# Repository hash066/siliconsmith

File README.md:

<div align="center">

# Hardwright

**Agents that design hardware, and prove it.**

<sub>Click the animation to watch the full demo video on YouTube.</sub>

[**Try it, no sign-up**](https://siliconsmith.vercel.app) · [**Watch the demo**](https://youtu.be/6LJNFYmQQWk) · [**Use it from your agent**](https://siliconsmith.vercel.app/connect) · [Feedback on Nebius](docs/feedback.md) · [Model comparison](docs/MODEL_COMPARISON.md)

</div>

Hardwright is a workstation for people who make hardware: describe a heat sink, a sensor board or a slow loop in plain words, and a
Nemotron agent builds it. Every claim it makes has to pass a checker it cannot argue with, so you get a part, a board or an instruction
you can open in a real tool, plus the evidence for it. It also ships as an **open-source Python package, command-line tool and MCP server**
so any coding agent can use the same checkers.

> Built for the Nebius x NVIDIA Global AI Hackathon (Coding and Agentic Engineering) · Apache-2.0

```bash
pip install "hardwright[matter] @ git+https://github.com/hash066/siliconsmith#subdirectory=engine"
claude mcp add hardwright -- hardwright mcp        # or: codex mcp add ... / Cursor / VS Code (see /connect)
hardwright board check --template fault_gpio12_vs_gpio14     # exit 1: the firmware uses a boot-strapping pin
```

---

## Three workbenches, one idea

The idea: **an AI may say what it likes, but it may only claim what a deterministic verifier returned.** Each workbench ends in something
you can open in a real tool, and each result carries the tool, the version and the verdict behind it.

| Workbench | You say | You get | Verified by |
|---|---|---|---|
| **Board** | "A battery ESP32 sensor board with a BME280 and USB-C charging; check it against its firmware." | A **routed 2-layer KiCad board** you can zoom, a schematic, a report card, Gerbers, KiCad file, BOM, pick-and-place. The wrong pin is marked on the pad. | Five netlist checks (B1 to B5: well formed, electrical rules, bus rules, firmware pins vs netlist and boot-strapping hazards, battery estimate), KiCad 7 design-rule check, the autorouter's completion |
| **Matter** | "A heat sink for a 5 W chip, 40 mm square, under 70 C." | A 3D part coloured by temperature, a printable **STL**, and a side-by-side with plain fins that use the same material | A finite-volume solver validated on analytic cases, an independent finite-element solver, printability rules, equal-material baselines (M1 to M5) |
| **Silicon** | "Make this loop faster with a custom RISC-V instruction." | A new instruction written **live**: Verilog, C intrinsic, rewritten kernel, a circuit view of the hardware, a waveform on real operand pairs, a before/after loop | Verilator lint, 1,000,000 test vectors, a **Yosys SAT proof for every possible input**, whole-program output check, cycle count and area |

Around them: a **chat agent** (Nemotron 3 Ultra, Super and Nano on Nebius Token Factory, with native tool calling) that performs actions in the app
and reports what it spent; **projects** (each workbench is a folder of projects with its own chat and settings); a **Workflow** tab that shows every
project as connected steps with their real status; a **Verified-by ledger** on every Proof tab; **one-click zip** of a project; and $0.50 of demo
credit per visitor from a $25 pool.

### See it

| Matter | Board |
|---|---|
|  |  |
| **Board, catching a mistake** | **Silicon** |
|  |  |

## What is real

Everything below ran for real and is reproducible; numbers are from the run logs and the test suites.

* **Board.** The three example boards (clean, wiring fault, strapping-pin fault) route fully with **0 KiCad errors** (15 silkscreen warnings), 48 × 36 mm.
  Boards for **any** design are made on request in a **Token Factory Sandbox** that has KiCad, Java and Freerouting: a custom design routed in **107 s**
  with 0 errors, measured on the public site. Placement is deterministic code (not a model), so a board is reproducible. Pin tables are cross-checked
  against KiCad's own symbol library. The checker is tested against a catalogue of 8 injected wiring faults.
* **Silicon, live.** A real run on the public site: Nemotron Ultra proposes, Super implements, a Sandbox proves it. TinyMaix int8 dot product:
  **3.32× fewer cycles for +4.8% area** (another run 2.69×), about 2 minutes and $0.04 of model tokens; ChaCha20: 1.14×. The recorded 20-minute full searches
  (with clock-speed estimates) reached **4.04× cycles / 3.76× wall-clock** on TinyMaix ([pull request](https://github.com/hash066/TinyMaix/pull/1)).
* **Matter.** Gains over an equal-material plain-fin plate are small and we say so: +0.1 to +0.5 K in the recorded evaluations, and the app will show a loss
  ("1.3 K hotter than plain fins") rather than hide it.
* **Tests.** Engine 640 passed (14 skipped), web 339 passed, axe accessibility 0 violations, layout shift 0.03, strict first-time-user pass in
  `docs/EVALUATION.md`.

## Honest limits

* The board check is **netlist level**. It does not prove a board works; the routed board is **not fabricated or tested electrically**. Part facts are
  author-curated, each with a `citation_checked` flag. 2 layers, 0.2 mm tracks, 0.15 mm clearance.
* Matter is **2D steady state** with stated constants: not CFD, not a measurement. "Validated" means agreement with analytic cases, nothing more.
* A live Silicon run skips clock-speed (place and route) so it reports **cycles and area, not wall-clock**; the recorded searches do include it.
  The FPGA rung (L6) was not run on a board. Software calls the instruction through inline assembly, not a compiler backend.
* The agent can be wrong: its answers are checked against the verifiers and say so when a check fails. Rate limits and the shared credit pool are per server instance.
* Run-to-run variance is real and published: TinyMaix wall-clock across our runs ranged 3.17× to 3.86×.

## Use it from your coding agent

The `hardwright` package (in `engine/`, Apache-2.0) is offline and free: no model, no network, no API key. Every check answers `pass`, `fail` or `unknown`;
only `pass` is a claim.

```python
import hardwright as hw
hw.board_check(template="fault_gpio12_vs_gpio14")["passed"]                       # False (B4)
hw.board_fix_pin(template="fault_gpio12_vs_gpio14", function="wake_btn", pin="GPIO14")["passed"]   # True
hw.matter_simulate(power_w=5, stl_path="heat-sink.stl")["peak_c"]
```

MCP tools: `board_templates`, `board_get_template`, `board_check`, `board_fix_pin`, `board_parts`, `matter_simulate`. Verified with the official MCP Python client.
Setup lines for Claude Code, Codex, Cursor, VS Code and Claude Desktop: `hardwright mcp --setup` or https://siliconsmith.vercel.app/connect.

## How it is built

### The big picture

```mermaid
flowchart LR
    you([You]) --> web["Next.js app<br/>Vercel"]
    agentx([Claude Code · Cursor · Codex]) -- MCP --> pkg
    term([Terminal]) -- CLI --> pkg
    pkg["hardwright package<br/>offline CLI + MCP server"] --> chk
    web -- "/api proxy" --> api["Python API host<br/>FastAPI on Vercel"]
    api --> chk["Deterministic checkers<br/>board B1 to B5 · Matter solvers · evidence ids"]
    web -- "chat agent" --> nem
    api --> nem["Nemotron on Nebius Token Factory<br/>Ultra · Super · Nano · tool calling"]
    api --> sbx
    subgraph sbx ["Token Factory Sandboxes"]
        base["siliconsmith-base<br/>Verilator · Yosys · RISC-V GCC"]
        kicad["siliconsmith-kicad<br/>KiCad 7 · Java · Freerouting"]
    end
    classDef box fill:#101827,stroke:#3d63d9,color:#fff;
    class web,api,chk,nem,pkg box;
```

### The evidence rule: a model can only claim what a checker returned

```mermaid
sequenceDiagram
    autonumber
    actor U as You
    participant A as Nemotron agent
    participant C as Checker (no model)
    participant G as Post-check
    U->>A: Is this board OK to send to fab?
    A->>C: board_check(template)
    C-->>A: pass / fail / unknown + evidence ids
    A->>G: Draft answer with its claims
    G-->>G: Every claim needs an evidence id. Invented commands or runs are flagged
    G-->>U: Answer citing board:fault_gpio12_vs_gpio14#B4
    Note over C,U: Only a pass counts as a claim. Unknown never does.
```

### Silicon: from a prompt to a proven instruction

```mermaid
flowchart TD
    p["Prompt: make this loop faster"] --> u["Nemotron Ultra<br/>proposes one custom RISC-V instruction"]
    u --> s["Nemotron Super<br/>writes the Verilog, the C intrinsic, the rewritten kernel"]
    s --> l1["Lint"]
    subgraph box ["Token Factory Sandbox"]
        l1 --> l2["One million test vectors"] --> l3["Formal proof (Yosys SAT) for every input"] --> l4["Whole-program output match"] --> l5["Cycles and area"]
    end
    l5 --> ok["Verified instruction:<br/>RTL, intrinsic, report, evidence ids"]
    l1 -. fail .-> n["Nemotron Nano<br/>triages the log"]
    l2 -. fail .-> n
    l3 -. counterexample .-> n
    l4 -. fail .-> n
    n --> r["Super repairs"] --> l1
```

### Components

* **Nemotron.** Ultra is the architect (proposals, diagnosis), Super the engineer (Verilog, C, repairs, the independent spec), Nano triages. Every call is logged
  with tokens and cost; a chat turn costs about $0.003 to $0.02, a live Silicon run $0.04 to $0.07.
* **Token Factory Sandboxes.** Everything model-written (Verilog, C) runs only inside a Sandbox: the live Silicon run, and the routing of every generated board.
  The full search runs each candidate from its parent's checkpoint image (21 Sandbox runs, up to 8 at once, in the headline run).
* **The evidence rule.** A claim in the UI carries an evidence id (`part:esp32.gpio12.strapping`, `board:fault_gpio12_vs_gpio14#B4`, `run:...`). The agent's
  answers are post-checked: an invented command or a claimed run that did not happen is flagged.
* **Library.** `evidence/` holds three verified instructions that anyone can re-check with no model: `siliconsmith verify-entry dot4-tinymaix`.
* **Model choice.** A small head-to-head against seven other models on the same endpoint is in [docs/MODEL_COMPARISON.md](docs/MODEL_COMPARISON.md), including where Nemotron is not the best.

## Run it locally

Requirements: Python 3.11+, Node 22, and for the full pipelines Linux or WSL2.

```bash
pip install -e "engine[matter,dev]"            # the checkers, CLI and MCP server
pytest engine/tests/test_hardwright_pkg.py      # package, CLI and MCP tests (no toolchain needed)
cd web && npm install && npm run dev            # the app; the hosted API is used unless LOCAL_PYTHON_API is set

# the full engine (Silicon search, KiCad layout) needs the toolchain:
sudo bash scripts/setup-toolchain.sh            # Verilator, Yosys, nextpnr, RISC-V GCC
pip install -e "engine[all]" && cp .env.example .env.local     # NEBIUS_API_KEY, NEBIUS_PROJECT_ID
siliconsmith accelerate w1 --backend contree    # the full Silicon search, every candidate in a Token Factory Sandbox
python -m siliconsmith.board.layout.build_sandbox_image         # build the KiCad Sandbox image (once)
```

Deploy notes, the Sandbox image recipes and every gotcha we hit are in `docs/HANDOFF_LATEST.md` and `docs/feedback.md`.

## Repository layout

```
engine/hardwright/          the open-source package: Python API, CLI, MCP server
engine/siliconsmith/        board/ (checker, layout, Sandbox routing), matter/ (solver), live/ (live Silicon), search, ladder, backends
engine/tests/               640 tests          engine/scripts/    build_boards.py (precomputes the template boards)
web/                        the app (Next.js)  web/public/boards/ the routed template boards
workloads/ hw/ firmware/    real kernels (TinyMaix, Monocypher), PicoRV32 SoC, runtime
evidence/                   verified instructions (re-checkable without a model)
docs/                       EVALUATION.md (strict evaluation), HANDOFF_LATEST.md, plans, feedback.md, video.md, devpost.md
```

## Related work, and what is new here

Commercial custom-instruction flows (Andes, Cadence Tensilica) build the processor after a human decides the instruction; research agents (CHIA, LACE) implement a
described extension; AI circuit-design tools (Flux Copilot and others) generate a design without a verifier that can refuse it. Hardwright puts a **deterministic
verifier between the model and every claim**, across chips (formal proof), boards (KiCad rules plus firmware-versus-datasheet checks) and matter (two independent solvers),
and ends each in a file you can open elsewhere.

## Licenses

Apache-2.0. Vendored or adapted code keeps its license: PicoRV32 (ISC), TinyMaix (Apache-2.0), Monocypher (BSD-2-Clause or CC0-1.0), KiCad footprints and symbols
(CC-BY-SA 4.0 with the library exception) and Freerouting (GPL-3.0, used only as a separate program inside the Sandbox image, never linked or redistributed here).

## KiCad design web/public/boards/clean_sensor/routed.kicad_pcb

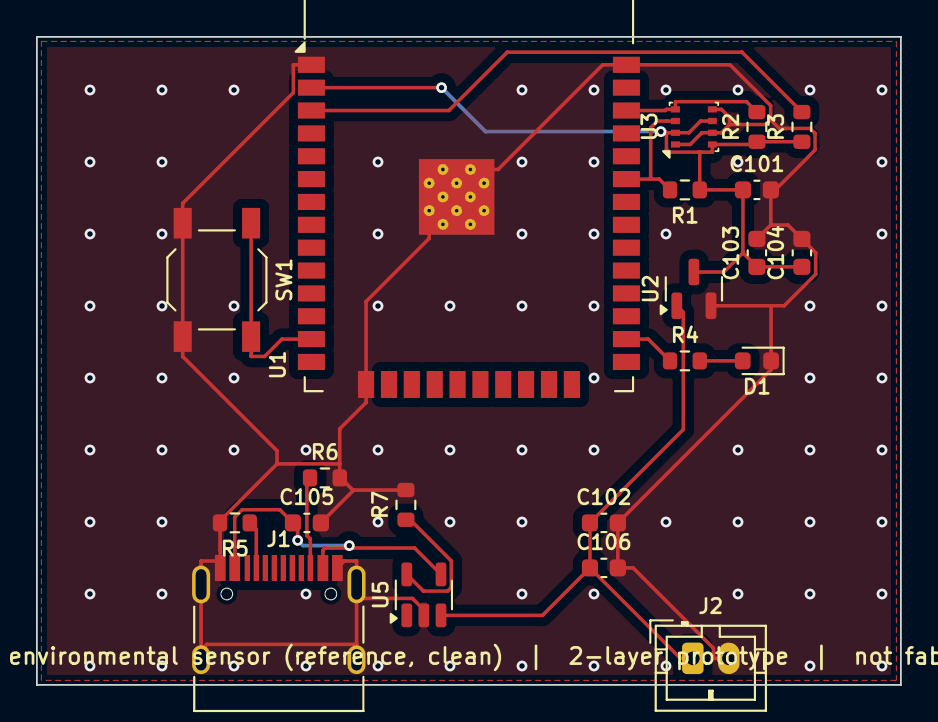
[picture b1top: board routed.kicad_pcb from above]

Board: 2 copper layers, 48.0 x 36.0 mm, 21 parts (0 on the bottom side), 13 nets.

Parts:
C101, C102, C103: 10u; C_0603_1608Metric
C104: 100n; C_0603_1608Metric
C105, C106: 4u7; C_0603_1608Metric
D1: LED (placeholder); LED_0603_1608Metric
J1: USB-C receptacle, power only (placeholder); USB_C_Receptacle_HRO_TYPE-C-31-M-12
J2: Li-ion cell connector (placeholder); JST_PH_B2B-PH-K_1x02_P2.00mm_Vertical
R1, R2: 4.7k; R_0603_1608Metric
R3: 10k; R_0603_1608Metric
R4: 330; R_0603_1608Metric
R5, R6: 5.1k; R_0603_1608Metric
R7: 2k; R_0603_1608Metric
SW1: Push button (placeholder); SW_SPST_TL3342
U1: ESP32-WROOM-32-class module; ESP32-WROOM-32
U2: Generic 3.3 V LDO (reference class, author-define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; SOT-23
U3: BME280-class humidity/pressure/temperature sensor; Bosch_LGA-8_2.5x2.5mm_P0.65mm_ClockwisePinNumbering
U5: MCP73831-class single-cell Li-ion charger (SOT-23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; SOT-23-5

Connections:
3V3: C101.1, C103.1, C104.1, R1.1, R2.1, R3.1, U1.2, U2.3, U3.2, U3.6, U3.8
CC1: J1.A5, R5.1
CC2: J1.B5, R6.1
EN: R3.2, U1.3
GND: C101.2, C102.2, C103.2, C104.2, C105.2, C106.2, D1.1, J1.A1, J1.A12, J1.B1, J1.B12, J1.S1, J2.2, R5.2, R6.2, R7.2, SW1.2, U1.1, U1.15, U1.38, U1.39, U2.2, U3.1, U3.5, U3.7, U5.2
LED_A: D1.2, R4.2
LED_DRV: R4.1, U1.26
PROG: R7.1, U5.5
SCL: R2.2, U1.36, U3.4
SDA: R1.2, U1.33, U3.3
VBAT: C102.1, C106.1, J2.1, U2.1, U5.3
VBUS: C105.1, J1.A4, J1.A9, J1.B4, J1.B9, U5.4
WAKE: SW1.1, U1.13

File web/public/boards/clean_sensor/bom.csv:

Refs,Qty,Value,Footprint,Source
C101 C102 C103,3,10u,Capacitor_SMD:C_0603_1608Metric,added by the layout (not in the checked netlist)
C104,1,100n,Capacitor_SMD:C_0603_1608Metric,added by the layout (not in the checked netlist)
C105 C106,2,4u7,Capacitor_SMD:C_0603_1608Metric,added by the layout (not in the checked netlist)
D1,1,LED (placeholder),LED_SMD:LED_0603_1608Metric,design
J1,1,"USB-C receptacle, power only (placeholder)",Connector_USB:USB_C_Receptacle_HRO_TYPE-C-31-M-12,design
J2,1,Li-ion cell connector (placeholder),Connector_JST:JST_PH_B2B-PH-K_1x02_P2.00mm_Vertical,design
R1 R2,2,4.7k,Resistor_SMD:R_0603_1608Metric,design
R3,1,10k,Resistor_SMD:R_0603_1608Metric,design
R4,1,330,Resistor_SMD:R_0603_1608Metric,design
R5 R6,2,5.1k,Resistor_SMD:R_0603_1608Metric,design
R7,1,2k,Resistor_SMD:R_0603_1608Metric,design
SW1,1,Push button (placeholder),Button_Switch_SMD:SW_SPST_TL3342,design
U1,1,ESP32-WROOM-32-class module,RF_Module:ESP32-WROOM-32,design
U2,1,"Generic 3.3 V LDO (reference class, author-defined values)",Package_TO_SOT_SMD:SOT-23,design
U3,1,BME280-class humidity/pressure/temperature sensor,Package_LGA:Bosch_LGA-8_2.5x2.5mm_P0.65mm_ClockwisePinNumbering,design
U5,1,MCP73831-class single-cell Li-ion charger (SOT-23-5),Package_TO_SOT_SMD:SOT-23-5,design

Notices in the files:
README.md:
License: Apache-2.0
